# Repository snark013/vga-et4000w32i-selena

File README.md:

# Selena VGA Card

[Русская версия](README_RU.md)

Main project repository: [git.snark13.com/snark13/selena](https://git.snark13.com/snark13/selena).

GitHub mirror: [github.com/snark013/vga-et4000w32i-selena](https://github.com/snark013/vga-et4000w32i-selena).

Selena is a VGA graphics card for the 16-bit ISA bus, based on the Tseng Labs ET4000/W32i. The project is designed in KiCad and uses a two-layer PCB.

Selena is based on Alexandru Groza’s [EXCELGRAPH ISA Video Display Controller](https://www.alexandrugroza.ro/microelectronics/system-design/isa-video-display-controller/index.html). It changes the component placement, routing, and video memory connections, and reduces the PCB layer count from four to two.

## Project status

Version 0.9.2 has been assembled and tested with both 1 MB and 2 MB of video memory. Memory interleaving works reliably with V53C16256HK50 chips.

Release files for version 1.0.2 are available in the repository. The test results above apply to version 0.9.2.

## Key features

- VGA compatibility.
- Fast video memory access in MS-DOS.
- Hardware graphics acceleration in Microsoft Windows.
- Video digital-to-analog converter (RAMDAC) with True Color support.
- Two video memory configurations: 1 MB or 2 MB.
- Two-layer PCB for the 16-bit ISA bus.

## Video memory configurations

| Capacity | Mode | Chips to populate | Notes |
| --- | --- | --- | --- |
| 1 MB | Linear | U4, U5 | Less demanding of the memory chips used. |
| 2 MB | Interleaved | U1, U2, U4, U5 | Offers higher performance; stability depends on the memory chips used. |

The 1 MB configuration can also accommodate chips that are unstable in the 2 MB interleaved configuration, without the additional CAS line delays used in the original project. Compatibility with specific chips must be verified on an assembled board.

## Project files

- [selena.kicad_pro](selena.kicad_pro) — KiCad project.
- [selena.kicad_sch](selena.kicad_sch) — schematic.
- [selena.kicad_pcb](selena.kicad_pcb) — PCB layout.
- [selena.pretty/](selena.pretty/) — local footprint library.
- [docs/](docs/) — reference documentation.
- [release/](release/) — release files: Gerber files, PDF schematics, and interactive bills of materials.
- [images/0.9.2/](images/0.9.2/) — photos of the assembled version 0.9.2 board.

### Release files

| Version | Gerber files | Schematic | Interactive bill of materials |
| --- | --- | --- | --- |
| 1.0.2 | [ZIP](release/1.0.2/gerbers-1.0.zip) | [PDF](release/1.0.2/selena.pdf) | [HTML](release/1.0.2/ibom.html) |
| 0.9.2 | [ZIP](release/0.9.2/gerbers.zip) | [PDF](release/0.9.2/selena.pdf) | [HTML](release/0.9.2/ibom.html) |

## Revision history

### 1.0.2

- Corrected PCB markings.
- Connected pin 3 of the ICS2494-304 clock generator to ground as specified in its documentation.

### 0.9.2

- Optimized component placement and video memory bus routing; memory chips are placed on both sides of the PCB.
- Changed the video memory connections from the original design and added a 1 MB configuration using two memory chips.
- Changed all capacitors below 0.1 µF to the 0805 package size.
- Renumbered components.

### 0.7

- Added support for mounting the RAMDAC in a PLCC44 socket.
- Added an alternative footprint for the video clock generator: U'3 can be populated instead of U3. Supported options are the CH9294E in DIP or SOIC packages and the ICS2494-304 in an SOIC package.

### 0.3

- Initial project version.

## Photos

Assembled version 0.9.2 board.

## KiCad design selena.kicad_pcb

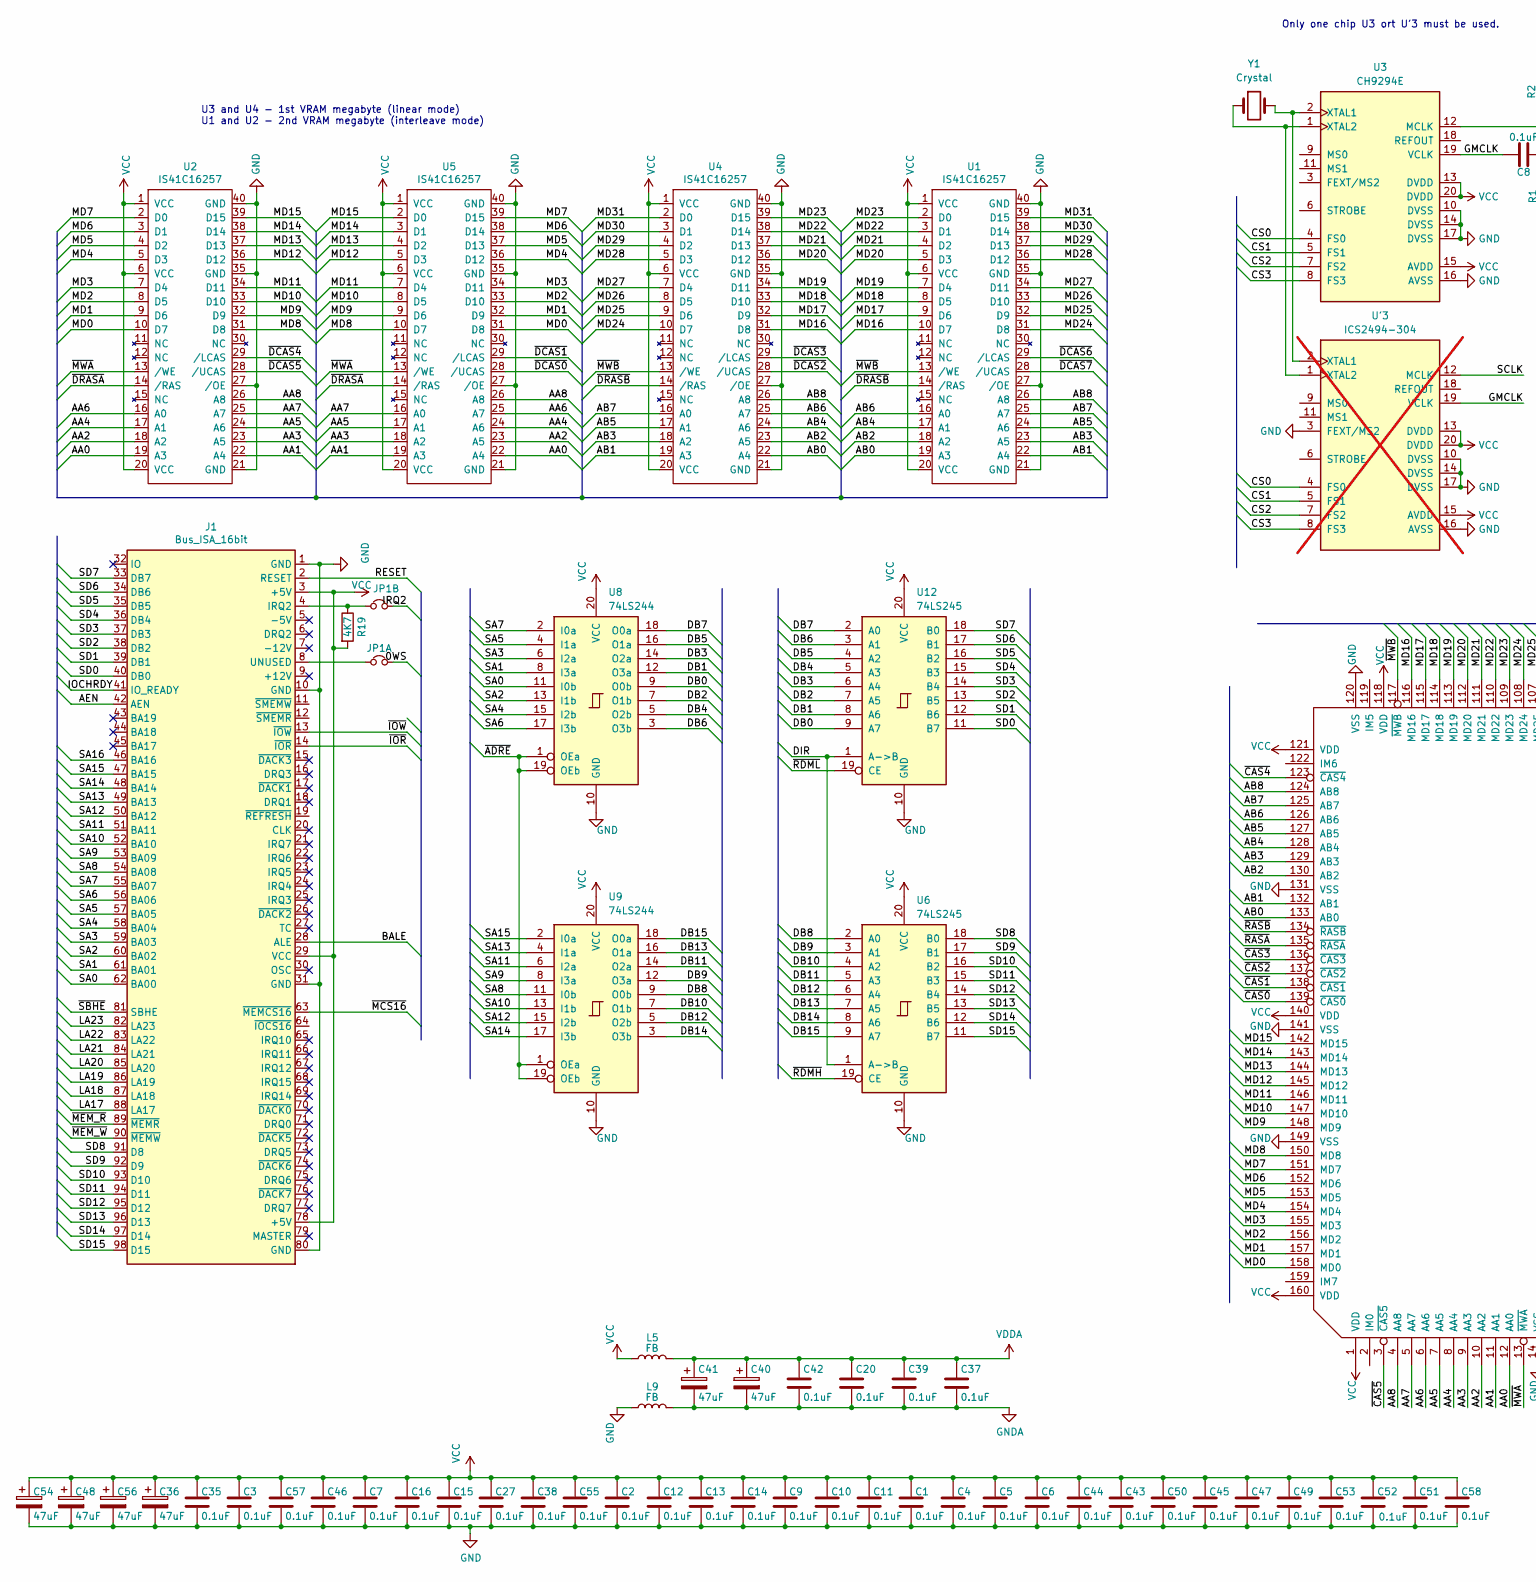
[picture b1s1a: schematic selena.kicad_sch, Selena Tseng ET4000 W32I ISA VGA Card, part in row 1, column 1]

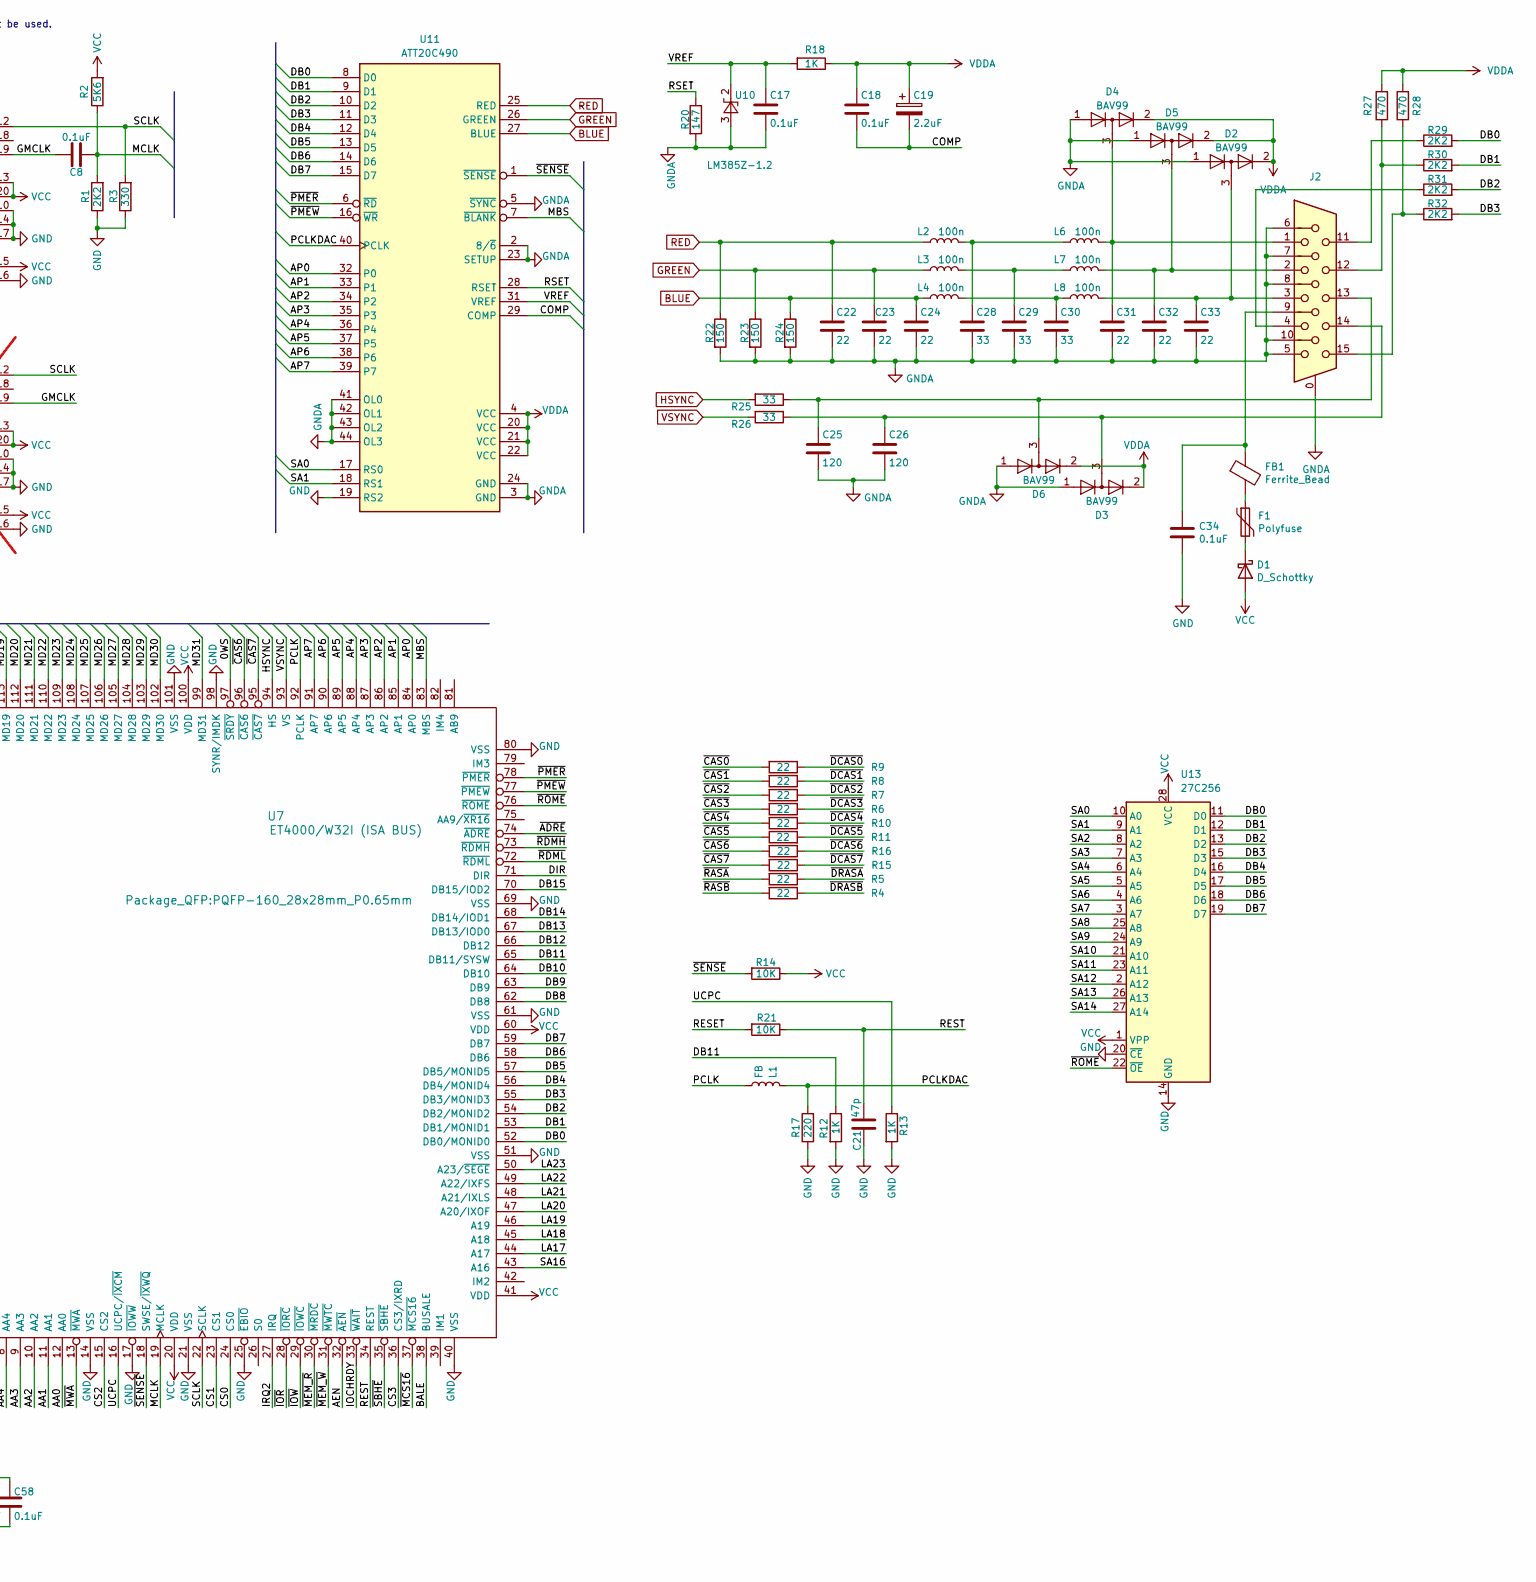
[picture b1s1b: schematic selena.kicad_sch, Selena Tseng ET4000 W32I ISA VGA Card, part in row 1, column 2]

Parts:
C1, C2, C3, C4, C5, C6, C7, C8, C9, C10, C11, C12, C13, C14, C15, C16, C17, C20, C27, C34, C35, C37, C38, C39, C42, C43, C44, C45, C46, C47, C49, C50, C51, C52, C53, C55, C57, C58: 0.1uF; C_0805_2012Metric
C18: 0.1uF; C_0603_1608Metric
C19: 2.2uF; CP_EIA-3216-18_Kemet-A
C21: 47p; C_0603_1608Metric
C22, C23, C24, C31, C32, C33: 22; C_0603_1608Metric
C25, C26: 120; C_0603_1608Metric
C28, C29, C30: 33; C_0603_1608Metric
C36, C40, C41, C48, C54, C56: 47uF; CP_EIA-3216-18_Kemet-A
D1: D_Schottky; D_MELF-RM10_Universal_Handsoldering
D2, D3, D4, D5, D6: BAV99; SOT-23
F1: Polyfuse; Fuse_0805_2012Metric_Pad1.15x1.40mm_HandSolder
FB1: Ferrite_Bead; L_0805_2012Metric_Pad1.15x1.40mm_HandSolder
J1: Bus_ISA_16bit; BUS_AT
J2: DB15_Female_HighDensity_MountingHoles; DSUB-15-HD_Female_Horizontal_P2.29x1.98mm_EdgePinOffset3.03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
JP1: 0WS; PinHeader_2x02_P2.54mm_Vertical
L1: FB; L_1206_3216Metric_Pad1.22x1.90mm_HandSolder
L2, L3, L4, L6, L7, L8: 100n; L_0805_2012Metric_Pad1.15x1.40mm_HandSolder
L5, L9: FB; L_0805_2012Metric_Pad1.15x1.40mm_HandSolder
R1, R29, R30, R31, R32: 2K2; R_0603_1608Metric
R2: 5K6; R_0603_1608Metric
R3: 330; R_0603_1608Metric
R4, R5, R6, R7, R8, R9, R10, R11, R15, R16: 22; R_0603_1608Metric
R12, R13, R18: 1K; R_0603_1608Metric
R14, R21: 10K; R_0603_1608Metric
R17: 220; R_0603_1608Metric
R19: 4K7; R_0603_1608Metric
R20: 147; R_0603_1608Metric
R22, R23, R24: 150; R_0603_1608Metric
R25, R26: 33; R_0603_1608Metric
R27, R28: 470; R_0603_1608Metric
U1, U2, U4, U5: IS41C16257; SOJ-40-Socket-LongPads
U3: CH9294E; DIP-20_W7.62mm_Socket
U6, U12: 74LS245; SOIC-20W_7.5x12.8mm_P1.27mm
U7: ET4000/W32I (ISA BUS); PQFP-160_28x28mm_P0.65mm
U8, U9: 74LS244; SOIC-20W_7.5x12.8mm_P1.27mm
U10: LM385Z-1.2; TO-92L
U11: ATT20C490; PLCC-44_SMD-Socket
U13: 27C256; DIP-28_W15.24mm_Socket
U'3: ICS2494-304; SOIC-20W_7.5x12.8mm_P1.27mm; not fitted
Y1: Crystal; Crystal_HC49-4H_Vertical

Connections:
/0WS: JP1.2, U7.97 (~SRDY)
/AA0: U2.19 (A3), U5.22 (A4), U7.12 (AA0)
/AA1: U2.22 (A4), U5.19 (A3), U7.11 (AA1)
/AA2: U2.18 (A2), U5.23 (A5), U7.10 (AA2)
/AA3: U2.23 (A5), U5.18 (A2), U7.9 (AA3)
/AA4: U2.17 (A1), U5.24 (A6), U7.8 (AA4)
/AA5: U2.24 (A6), U5.17 (A1), U7.7 (AA5)
/AA6: U2.16 (A0), U5.25 (A7), U7.6 (AA6)
/AA7: U2.25 (A7), U5.16 (A0), U7.5 (AA7)
/AA8: U2.26 (A8), U5.26 (A8), U7.4 (AA8)
/AB0: U1.19 (A3), U4.22 (A4), U7.133 (AB0)
/AB1: U1.22 (A4), U4.19 (A3), U7.132 (AB1)
/AB2: U1.18 (A2), U4.23 (A5), U7.130 (AB2)
/AB3: U1.23 (A5), U4.18 (A2), U7.129 (AB3)
/AB4: U1.17 (A1), U4.24 (A6), U7.128 (AB4)
/AB5: U1.24 (A6), U4.17 (A1), U7.127 (AB5)
/AB6: U1.16 (A0), U4.25 (A7), U7.126 (AB6)
/AB7: U1.25 (A7), U4.16 (A0), U7.125 (AB7)
/AB8: U1.26 (A8), U4.26 (A8), U7.124 (AB8)
/AEN: J1.42 (AEN), U7.32 (~AEN)
/AP0: U7.84 (AP0), U11.32 (P0)
/AP1: U7.85 (AP1), U11.33 (P1)
/AP2: U7.86 (AP2), U11.34 (P2)
/AP3: U7.87 (AP3), U11.35 (P3)
/AP4: U7.88 (AP4), U11.36 (P4)
/AP5: U7.89 (AP5), U11.37 (P5)
/AP6: U7.90 (AP6), U11.38 (P6)
/AP7: U7.91 (AP7), U11.39 (P7)
/BALE: J1.28 (ALE), U7.38 (BUSALE)
/COMP: C18.2, C19.2, U11.29 (COMP)
/CS0: U3.4 (FS0), U7.24 (CS0), U'3.4 (FS0)
/CS1: U3.5 (FS1), U7.23 (CS1), U'3.5 (FS1)
/CS2: U3.7 (FS2), U7.15 (CS2), U'3.7 (FS2)
/CS3: U3.8 (FS3), U7.36 (CS3/IXRD), U'3.8 (FS3)
/DB0: R29.2, U7.52 (DB0/MONID0), U8.9 (O0b), U11.8 (D0), U12.9 (A7), U13.11 (D0)
/DB1: R30.2, U7.53 (DB1/MONID1), U8.12 (O3a), U11.9 (D1), U12.8 (A6), U13.12 (D1)
/DB2: R31.2, U7.54 (DB2/MONID2), U8.7 (O1b), U11.10 (D2), U12.7 (A5), U13.13 (D2)
/DB3: R32.2, U7.55 (DB3/MONID3), U8.14 (O2a), U11.11 (D3), U12.6 (A4), U13.15 (D3)
/DB4: U7.56 (DB4/MONID4), U8.5 (O2b), U11.12 (D4), U12.5 (A3), U13.16 (D4)
/DB5: U7.57 (DB5/MONID5), U8.16 (O1a), U11.13 (D5), U12.4 (A2), U13.17 (D5)
/DB6: U7.58 (DB6), U8.3 (O3b), U11.14 (D6), U12.3 (A1), U13.18 (D6)
/DB7: U7.59 (DB7), U8.18 (O0a), U11.15 (D7), U12.2 (A0), U13.19 (D7)
/DB8: U6.2 (A0), U7.62 (DB8), U9.9 (O0b)
/DB9: U6.3 (A1), U7.63 (DB9), U9.12 (O3a)
/DB10: U6.4 (A2), U7.64 (DB10), U9.7 (O1b)
/DB11: R12.1, U6.5 (A3), U7.65 (DB11/SYSW), U9.14 (O2a)
/DB12: U6.6 (A4), U7.66 (DB12), U9.5 (O2b)
/DB13: U6.7 (A5), U7.67 (DB13/IOD0), U9.16 (O1a)
/DB14: U6.8 (A6), U7.68 (DB14/IOD1), U9.3 (O3b)
/DB15: U6.9 (A7), U7.70 (DB15/IOD2), U9.18 (O0a)
/DIR: U6.1 (A->B), U7.71 (DIR), U12.1 (A->B)
/GMCLK: C8.1, U3.19 (VCLK), U'3.19 (VCLK)
/IOCHRDY: J1.41 (IO_READY), U7.33 (~WAIT)
/IRQ2: JP1.4, U7.27 (IRQ)
/LA17: J1.88 (LA17), U7.44 (A17)
/LA18: J1.87 (LA18), U7.45 (A18)
/LA19: J1.86 (LA19), U7.46 (A19)
/LA20: J1.85 (LA20), U7.47 (A20/IXOF)
/LA21: J1.84 (LA21), U7.48 (A21/IXLS)
/LA22: J1.83 (LA22), U7.49 (A22/IXFS)
/LA23: J1.82 (LA23), U7.50 (A23/~SEGE)
/MBS: U7.83 (MBS), U11.7 (~BLANK)
/MCLK: C8.2, R1.2, R2.1, U7.19 (MCLK)
/MD0: U2.10 (D7), U5.31 (D8), U7.158 (MD0)
/MD1: U2.9 (D6), U5.32 (D9), U7.157 (MD1)
/MD2: U2.8 (D5), U5.33 (D10), U7.156 (MD2)
/MD3: U2.7 (D4), U5.34 (D11), U7.155 (MD3)
/MD4: U2.5 (D3), U5.36 (D12), U7.154 (MD4)
/MD5: U2.4 (D2), U5.37 (D13), U7.153 (MD5)
/MD6: U2.3 (D1), U5.38 (D14), U7.152 (MD6)
/MD7: U2.2 (D0), U5.39 (D15), U7.151 (MD7)
/MD8: U2.31 (D8), U5.10 (D7), U7.150 (MD8)
/MD9: U2.32 (D9), U5.9 (D6), U7.148 (MD9)
/MD10: U2.33 (D10), U5.8 (D5), U7.147 (MD10)
/MD11: U2.34 (D11), U5.7 (D4), U7.146 (MD11)
/MD12: U2.36 (D12), U5.5 (D3), U7.145 (MD12)
/MD13: U2.37 (D13), U5.4 (D2), U7.144 (MD13)
/MD14: U2.38 (D14), U5.3 (D1), U7.143 (MD14)
/MD15: U2.39 (D15), U5.2 (D0), U7.142 (MD15)
/MD16: U1.10 (D7), U4.31 (D8), U7.116 (MD16)
/MD17: U1.9 (D6), U4.32 (D9), U7.115 (MD17)
/MD18: U1.8 (D5), U4.33 (D10), U7.114 (MD18)
/MD19: U1.7 (D4), U4.34 (D11), U7.113 (MD19)
/MD20: U1.5 (D3), U4.36 (D12), U7.112 (MD20)
/MD21: U1.4 (D2), U4.37 (D13), U7.111 (MD21)
/MD22: U1.3 (D1), U4.38 (D14), U7.110 (MD22)
/MD23: U1.2 (D0), U4.39 (D15), U7.109 (MD23)
/MD24: U1.31 (D8), U4.10 (D7), U7.108 (MD24)
/MD25: U1.32 (D9), U4.9 (D6), U7.107 (MD25)
/MD26: U1.33 (D10), U4.8 (D5), U7.106 (MD26)
/MD27: U1.34 (D11), U4.7 (D4), U7.105 (MD27)
/MD28: U1.36 (D12), U4.5 (D3), U7.104 (MD28)
/MD29: U1.37 (D13), U4.4 (D2), U7.103 (MD29)
/MD30: U1.38 (D14), U4.3 (D1), U7.102 (MD30)
/MD31: U1.39 (D15), U4.2 (D0), U7.99 (MD31)
/PCLK: L1.2, U7.92 (PCLK)
/PCLKDAC: L1.1, R17.2, U11.40 (PCLK)
/RESET: J1.2 (RESET), R21.2
/REST: C21.2, R21.1, U7.34 (REST)
/RSET: R20.1, U11.28 (RSET)
/SA0: J1.62 (BA00), U8.11 (I0b), U11.17 (RS0), U13.10 (A0)
/SA1: J1.61 (BA01), U8.8 (I3a), U11.18 (RS1), U13.9 (A1)
/SA2: J1.60 (BA02), U8.13 (I1b), U13.8 (A2)
/SA3: J1.59 (BA03), U8.6 (I2a), U13.7 (A3)
/SA4: J1.58 (BA04), U8.15 (I2b), U13.6 (A4)
/SA5: J1.57 (BA05), U8.4 (I1a), U13.5 (A5)
/SA6: J1.56 (BA06), U8.17 (I3b), U13.4 (A6)
/SA7: J1.55 (BA07), U8.2 (I0a), U13.3 (A7)
/SA8: J1.54 (BA08), U9.11 (I0b), U13.25 (A8)
/SA9: J1.53 (BA09), U9.8 (I3a), U13.24 (A9)
/SA10: J1.52 (BA10), U9.13 (I1b), U13.21 (A10)
/SA11: J1.51 (BA11), U9.6 (I2a), U13.23 (A11)
/SA12: J1.50 (BA12), U9.15 (I2b), U13.2 (A12)
/SA13: J1.49 (BA13), U9.4 (I1a), U13.26 (A13)
/SA14: J1.48 (BA14), U9.17 (I3b), U13.27 (A14)
/SA15: J1.47 (BA15), U9.2 (I0a)
/SA16: J1.46 (BA16), U7.43 (A16)
/SCLK: R3.2, U3.12 (MCLK), U7.22 (SCLK), U'3.12 (MCLK)
/SD0: J1.40 (DB0), U12.11 (B7)
/SD1: J1.39 (DB1), U12.12 (B6)
/SD2: J1.38 (DB2), U12.13 (B5)
/SD3: J1.37 (DB3), U12.14 (B4)
/SD4: J1.36 (DB4), U12.15 (B3)
/SD5: J1.35 (DB5), U12.16 (B2)
/SD6: J1.34 (DB6), U12.17 (B1)
/SD7: J1.33 (DB7), U12.18 (B0)
/SD8: J1.91 (D8), U6.18 (B0)
/SD9: J1.92 (D9), U6.17 (B1)
/SD10: J1.93 (D10), U6.16 (B2)
/SD11: J1.94 (D11), U6.15 (B3)
/SD12: J1.95 (D12), U6.14 (B4)
/SD13: J1.96 (D13), U6.13 (B5)
/SD14: J1.97 (D14), U6.12 (B6)
/SD15: J1.98 (D15), U6.11 (B7)
/UCPC: R13.1, U7.16 (UCPC/~IXCM)
/VREF: C17.1, R18.2, U10.2 (K), U11.31 (VREF)
/~ADRE: U7.74 (~ADRE), U8.1 (OEa), U8.19 (OEb), U9.1 (OEa), U9.19 (OEb)
/~CAS0: R9.2, U7.139 (~CAS0)
/~CAS1: R8.2, U7.138 (~CAS1)
/~CAS2: R7.2, U7.137 (~CAS2)
/~CAS3: R6.2, U7.136 (~CAS3)
/~CAS4: R10.2, U7.123 (~CAS4)
/~CAS5: R11.1, U7.3 (~CAS5)
/~CAS6: R16.2, U7.96 (~CAS6)
/~CAS7: R15.2, U7.95 (~CAS7)
/~DCAS0: R9.1, U5.28 (/UCAS)
/~DCAS1: R8.1, U5.29 (/LCAS)
/~DCAS2: R7.1, U4.28 (/UCAS)
/~DCAS3: R6.1, U4.29 (/LCAS)
/~DCAS4: R10.1, U2.29 (/LCAS)
/~DCAS5: R11.2, U2.28 (/UCAS)
/~DCAS6: R16.1, U1.29 (/LCAS)
/~DCAS7: R15.1, U1.28 (/UCAS)
/~DRASA: R5.1, U2.14 (/RAS), U5.14 (/RAS)
/~DRASB: R4.1, U1.14 (/RAS), U4.14 (/RAS)
/~IOR: J1.14 (~IOR), U7.28 (~IORC)
/~IOW: J1.13 (~IOW), U7.29 (~IOWC)
/~MCS16: J1.63 (~MEMCS16), U7.37 (~MCS16)
/~MEM_R: J1.89 (~MEMR), U7.30 (~MRDC)
/~MEM_W: J1.90 (~MEMW), U7.31 (~MWTC)
/~MWA: U2.13 (/WE), U5.13 (/WE), U7.13 (~MWA)
/~MWB: U1.13 (/WE), U4.13 (/WE), U7.117 (~MWB)
/~PMER: U7.78 (~PMER), U11.6 (~RD)
/~PMEW: U7.77 (~PMEW), U11.16 (~WR)
/~RASA: R5.2, U7.135 (~RASA)
/~RASB: R4.2, U7.134 (~RASB)
/~RDMH: U6.19 (CE), U7.73 (~RDMH)
/~RDML: U7.72 (~RDML), U12.19 (CE)
/~ROME: U7.76 (~ROME), U13.22 (~OE)
/~SBHE: J1.81 (SBHE), U7.35 (~SBHE)
/~SENSE: R14.2, U7.18 (SWSE/~IXWQ), U11.1 (~SENSE)
BLUE: C24.1, L4.1, R24.1, U11.27 (BLUE)
GND: C1.2, C2.2, C3.2, C4.2, C5.2, C6.2, C7.2, C9.2, C10.2, C11.2, C12.2, C13.2, C14.2, C15.2, C16.2, C21.1, C27.2, C34.2, C35.2, C36.2, C38.2, C43.2, C44.2, C45.2, C46.2, C47.2, C48.2, C49.2, C50.2, C51.2, C52.2, C53.2, C54.2, C55.2, C56.2, C57.2, C58.2, J1.1 (GND), J1.10 (GND), J1.31 (GND), J1.80 (GND), L9.1, R1.1, R3.1, R12.2, R13.2, R17.1, U1.21 (GND), U1.27 (/OE), U1.35 (GND), U1.40 (GND), U2.21 (GND), U2.27 (/OE), U2.35 (GND), U2.40 (GND), U3.10 (DVSS), U3.14 (DVSS), U3.16 (AVSS), U3.17 (DVSS), U4.21 (GND), U4.27 (/OE), U4.35 (GND), U4.40 (GND), U5.21 (GND), U5.27 (/OE), U5.35 (GND), U5.40 (GND), U6.10 (GND), U7.14 (VSS), U7.17 (~IOWW), U7.21 (VSS), U7.25 (~EBIO), U7.40 (VSS), U7.51 (VSS), U7.61 (VSS), U7.69 (VSS), U7.80 (VSS), U7.98 (SYNR/IMDK), U7.101 (VSS), U7.120 (VSS), U7.131 (VSS), U7.141 (VSS), U7.149 (VSS), U8.10 (GND), U9.10 (GND), U11.19 (RS2), U12.10 (GND), U13.14 (GND), U13.20 (~CE), U'3.3 (FEXT/MS2), U'3.10 (DVSS), U'3.14 (DVSS), U'3.16 (AVSS), U'3.17 (DVSS)
GNDA: C17.2, C20.2, C22.2, C23.2, C24.2, C25.2, C26.2, C28.2, C29.2, C30.2, C31.2, C32.2, C33.2, C37.2, C39.2, C40.2, C41.2, C42.2, D2.1 (K), D3.1 (K), D4.1 (K), D5.1 (K), D6.1 (K), J2.0, J2.5, J2.6, J2.7, J2.8, J2.10, L9.2, R20.2, R22.2, R23.2, R24.2, U10.3 (A), U11.2 (8/~6), U11.3 (GND), U11.5 (~SYNC), U11.23 (SETUP), U11.24 (GND), U11.41 (OL0), U11.42 (OL1), U11.43 (OL2), U11.44 (OL3)
GREEN: C23.1, L3.1, R23.1, U11.26 (GREEN)
HSYNC: R25.2, U7.94 (HS)
unnamed: C25.1, D6.3 (K), J2.13, R25.1
unnamed: C26.1, D3.3 (K), J2.14, R26.1
unnamed: C28.1, L2.2, L6.1
unnamed: C29.1, L3.2, L7.1
unnamed: C30.1, L4.2, L8.1
unnamed: C31.1, D4.3 (K), J2.1, L6.2
unnamed: C32.1, D5.3 (K), J2.2, L7.2
unnamed: C33.1, D2.3 (K), J2.3, L8.2
unnamed: C34.1, FB1.1, J2.9
unnamed: D1.1 (K), F1.2
unnamed: F1.1, FB1.2
unnamed: J1.4 (IRQ2), JP1.3, R19.1
unnamed: J1.8 (UNUSED), JP1.1
unnamed: J2.4, R31.1
unnamed: J2.11, R29.1
unnamed: J2.12, R27.1, R30.1
unnamed: J2.15, R28.1, R32.1
unnamed: U3.2 (XTAL1), U'3.2 (XTAL1), Y1.2
unnamed: U3.1 (XTAL2), U'3.1 (XTAL2), Y1.1
RED: C22.1, L2.1, R22.1, U11.25 (RED)
VCC: C1.1, C2.1, C3.1, C4.1, C5.1, C6.1, C7.1, C9.1, C10.1, C11.1, C12.1, C13.1, C14.1, C15.1, C16.1, C27.1, C35.1, C36.1, C38.1, C43.1, C44.1, C45.1, C46.1, C47.1, C48.1, C49.1, C50.1, C51.1, C52.1, C53.1, C54.1, C55.1, C56.1, C57.1, C58.1, D1.2 (A), J1.3 (+5V), J1.29 (VCC), J1.78 (+5V), L5.1, R2.2, R14.1, R19.2, U1.1 (VCC), U1.6 (VCC), U1.20 (VCC), U2.1 (VCC), U2.6 (VCC), U2.20 (VCC), U3.13 (DVDD), U3.15 (AVDD), U3.20 (DVDD), U4.1 (VCC), U4.6 (VCC), U4.20 (VCC), U5.1 (VCC), U5.6 (VCC), U5.20 (VCC), U6.20 (VCC), U7.1 (VDD), U7.20 (VDD), U7.41 (VDD), U7.60 (VDD), U7.100 (VDD), U7.118 (VDD), U7.121 (VDD), U7.140 (VDD), U7.160 (VDD), U8.20 (VCC), U9.20 (VCC), U12.20 (VCC), U13.1 (VPP), U13.28 (VCC), U'3.13 (DVDD), U'3.15 (AVDD), U'3.20 (DVDD)
VDDA: C18.1, C19.1, C20.1, C37.1, C39.1, C40.1, C41.1, C42.1, D2.2 (A), D3.2 (A), D4.2 (A), D5.2 (A), D6.2 (A), L5.2, R18.1, R27.2, R28.2, U11.4 (VCC), U11.20 (VCC), U11.21 (VCC), U11.22 (VCC)
VSYNC: R26.2, U7.93 (VS)

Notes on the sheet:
U3 and U4 - 1st VRAM megabyte (linear mode) U1 and U2 - 2nd VRAM megabyte (interleave mode)
Only one chip U3 ort U'3 must be used.

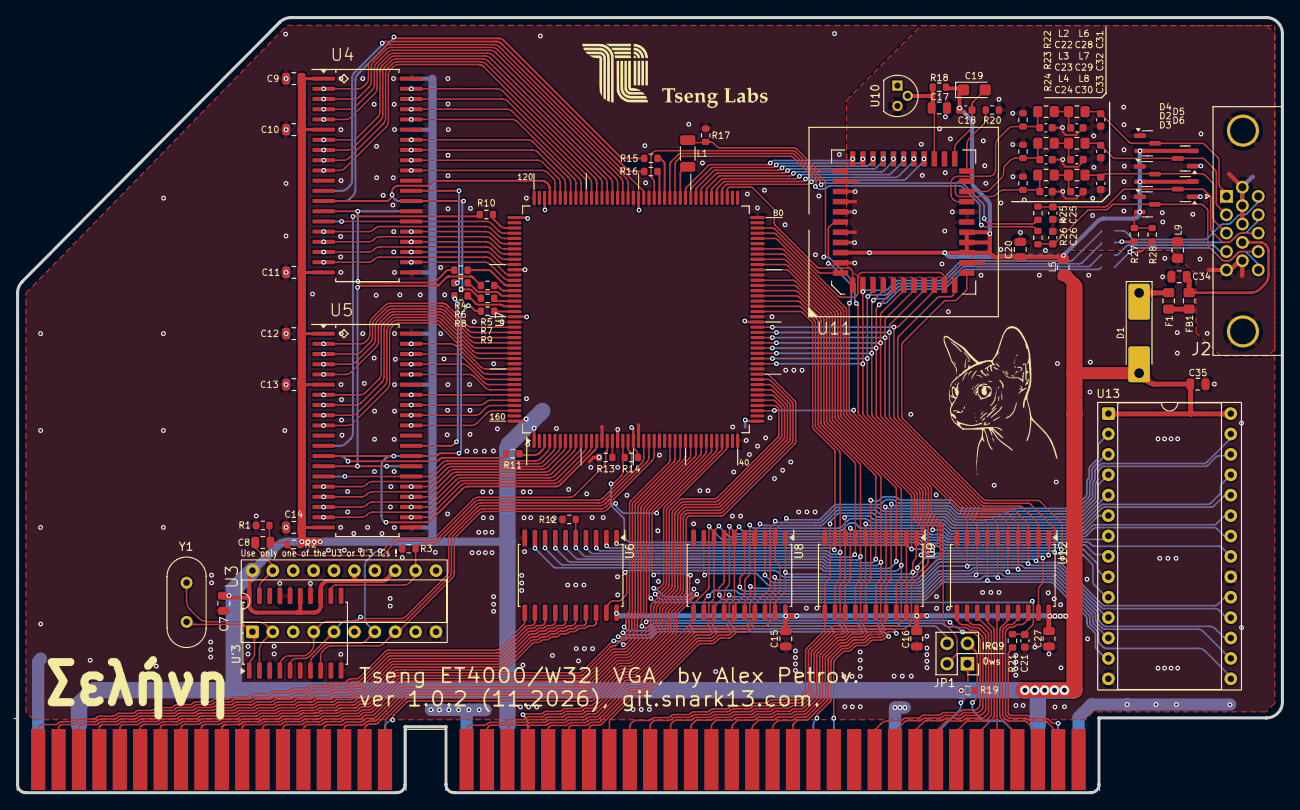
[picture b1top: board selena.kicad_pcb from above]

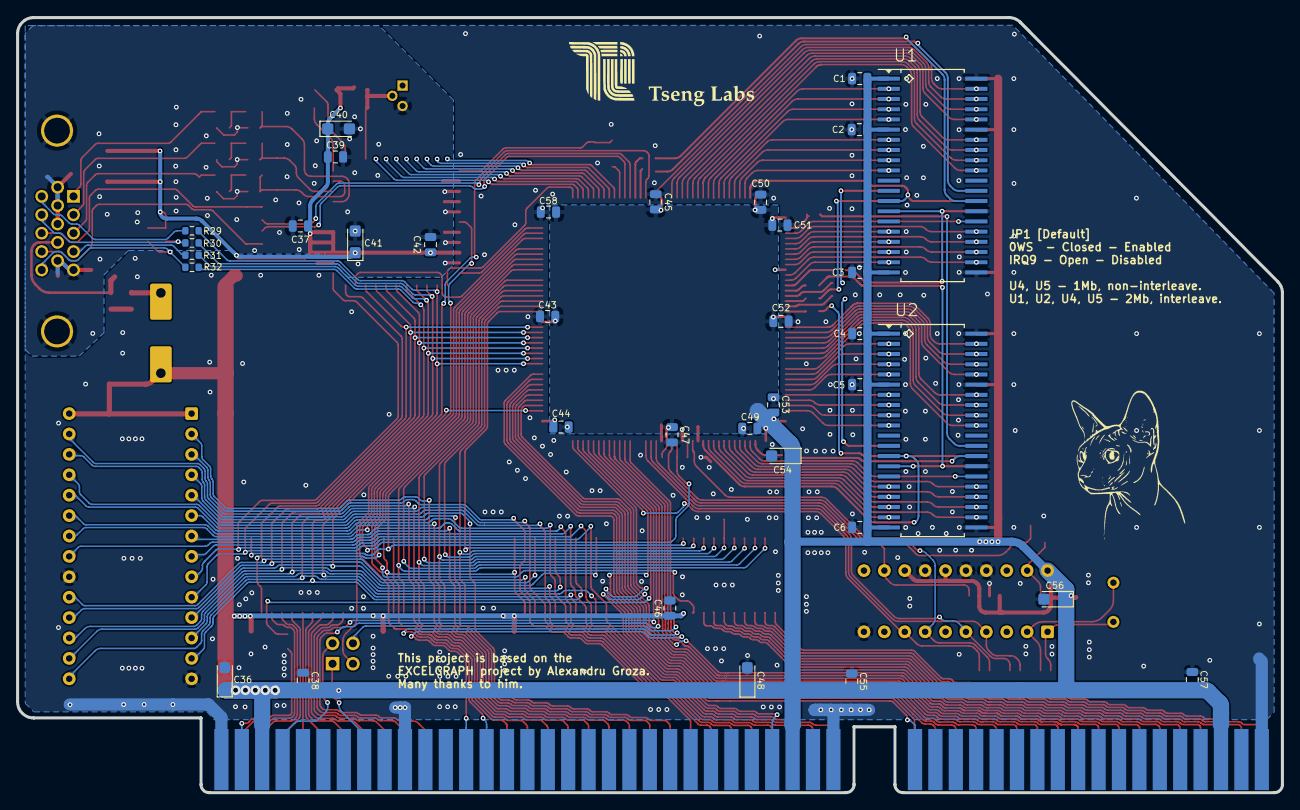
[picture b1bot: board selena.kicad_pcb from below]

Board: 2 copper layers, 157.5 x 96.5 mm, 125 parts (35 on the bottom side), 199 nets.

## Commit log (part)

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2025-09-13 Initial release
2025-09-13 Обновить README.md
2025-09-13 ChangeLog: - docs added.
2025-09-13 ChangeLog: - update README
2025-09-13 Release 0.9.2
